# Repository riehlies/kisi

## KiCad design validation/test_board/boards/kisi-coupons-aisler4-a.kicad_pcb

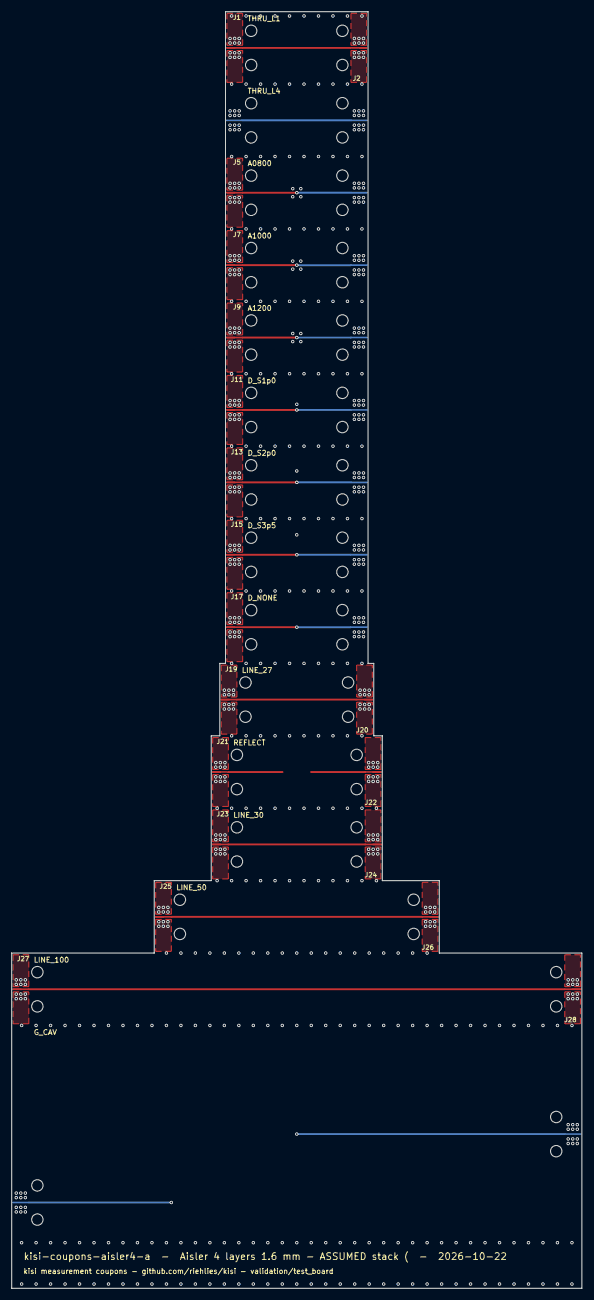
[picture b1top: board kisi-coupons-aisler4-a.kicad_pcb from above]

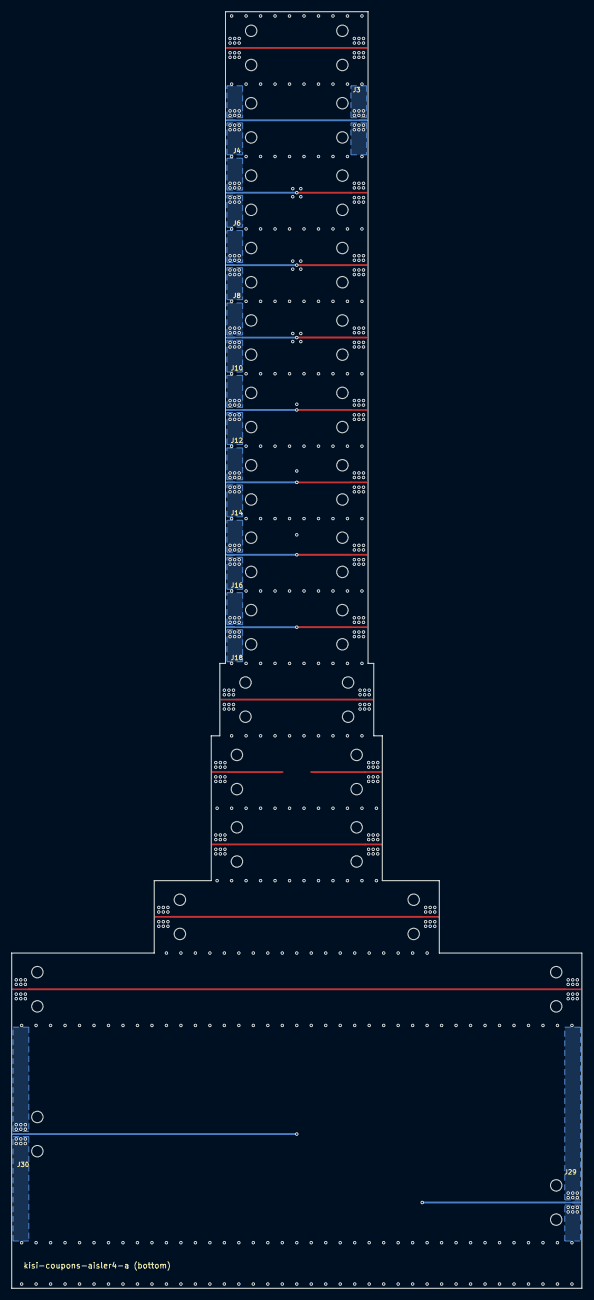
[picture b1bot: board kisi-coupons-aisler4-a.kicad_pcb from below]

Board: 4 copper layers, 100.0 x 223.9 mm, 30 parts (11 on the bottom side), 14 nets.

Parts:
J1, J2, J3, J4, J5, J6, J7, J8, J9, J10, J11, J12, J13, J14, J15, J16, J17, J18, J19, J20, J21, J22, J23, J24, J25, J26, J27, J28, J29, J30: 292-04A-14 / 1092-01A-14; SWM_EndLaunch_Narrow_PLACEHOLDER

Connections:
CAV: J29.1, J30.1
SE_A0800: J5.1, J6.1
SE_A1000: J7.1, J8.1
SE_A1200: J9.1, J10.1
SE_D_NONE: J17.1, J18.1
SE_D_S1p0: J11.1, J12.1
SE_D_S2p0: J13.1, J14.1
SE_D_S3p5: J15.1, J16.1
SE_LINE_27: J19.1, J20.1
SE_LINE_30: J23.1, J24.1
SE_LINE_50: J25.1, J26.1
SE_LINE_100: J27.1, J28.1
SE_THRU_L1: J1.1, J2.1
SE_THRU_L4: J3.1, J4.1

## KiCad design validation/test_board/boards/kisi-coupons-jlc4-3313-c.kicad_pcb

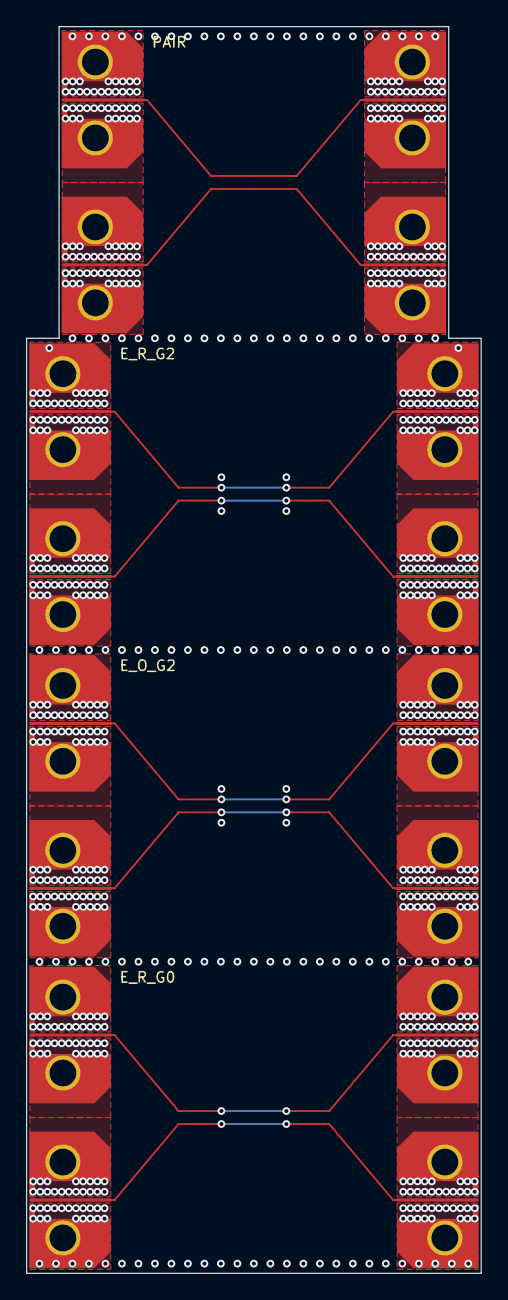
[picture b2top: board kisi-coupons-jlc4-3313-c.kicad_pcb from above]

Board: 4 copper layers, 35.0 x 96.0 mm, 16 parts (0 on the bottom side), 9 nets.

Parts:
J1, J2, J3, J4, J5, J6, J7, J8, J9, J10, J11, J12, J13, J14, J15, J16: 292-J-P-EP-ST-EL-01; Samtec_292-J-P-EP-ST-EL-01_EdgeLaunch_W0.255

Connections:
DP_E_O_G2_N: J10.1, J12.1
DP_E_O_G2_P: J9.1, J11.1
DP_E_R_G0_N: J14.1, J16.1
DP_E_R_G0_P: J13.1, J15.1
DP_E_R_G2_N: J6.1, J8.1
DP_E_R_G2_P: J5.1, J7.1
DP_PAIR_N: J2.1, J4.1
DP_PAIR_P: J1.1, J3.1
GND: J1.2, J1.3, J2.2, J2.3, J3.2, J3.3, J4.2, J4.3, J5.2, J5.3, J6.2, J6.3, J7.2, J7.3, J8.2, J8.3, J9.2, J9.3, J10.2, J10.3, J11.2, J11.3, J12.2, J12.3, J13.2, J13.3, J14.2, J14.3, J15.2, J15.3, J16.2, J16.3

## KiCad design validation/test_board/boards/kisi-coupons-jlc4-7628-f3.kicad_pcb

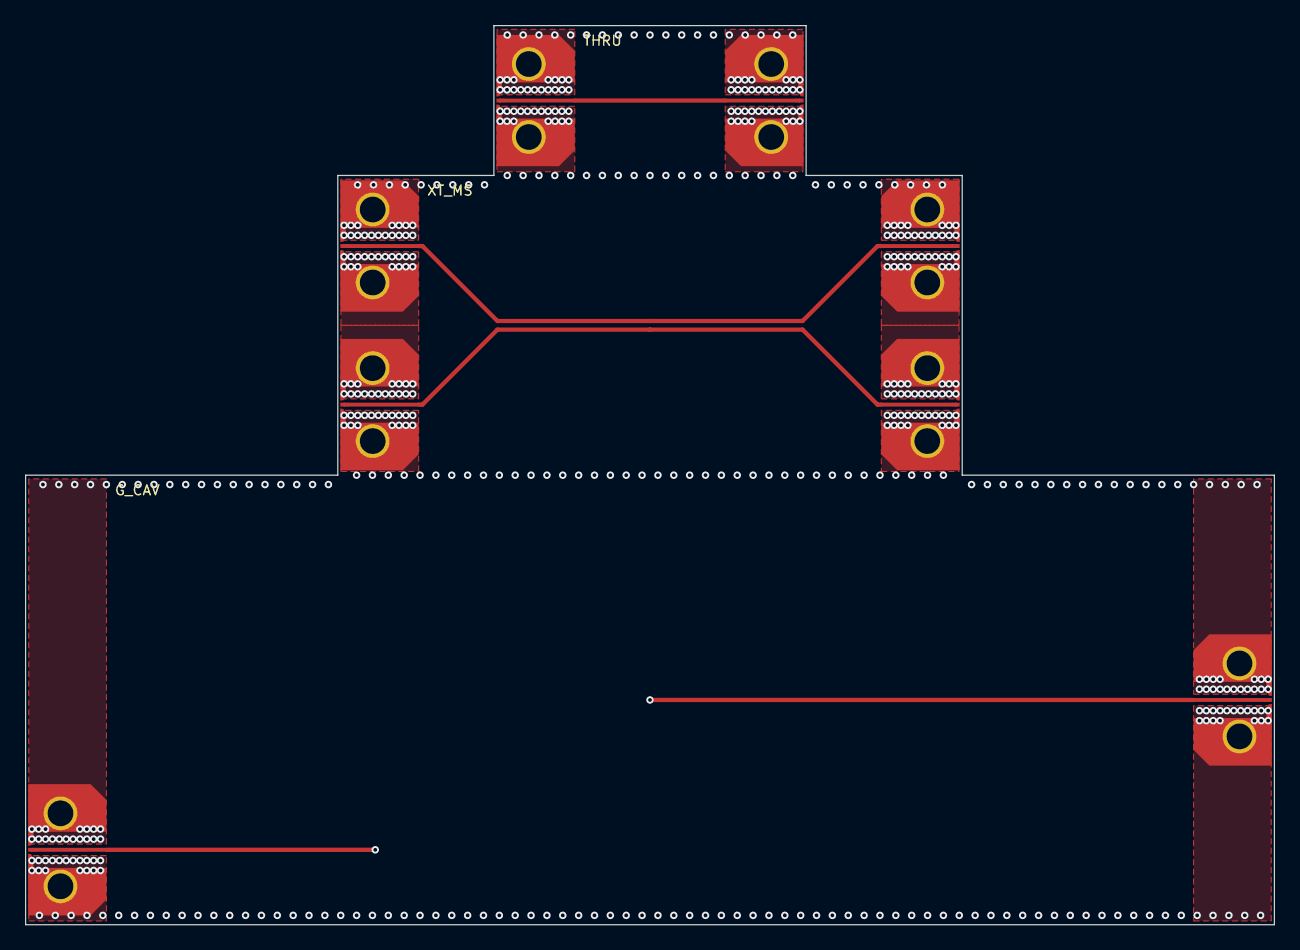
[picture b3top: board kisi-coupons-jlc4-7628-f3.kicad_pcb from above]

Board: 4 copper layers, 100.0 x 72.0 mm, 8 parts (0 on the bottom side), 5 nets.

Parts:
J1, J2, J3, J4, J5, J6, J7, J8: 292-J-P-EP-ST-EL-01; Samtec_292-J-P-EP-ST-EL-01_EdgeLaunch

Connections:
CAV_G_CAV: J7.1, J8.1
GND: J1.2, J1.3, J2.2, J2.3, J3.2, J3.3, J4.2, J4.3, J5.2, J5.3, J6.2, J6.3, J7.2, J7.3, J8.2, J8.3
SE_THRU: J1.1, J2.1
SE_XT_A: J3.1, J5.1
SE_XT_V: J4.1, J6.1
